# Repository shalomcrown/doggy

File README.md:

# doggy

Things to do with robot dogs. Firmware for a Freenove robot dog on **Raspberry Pi aarch64** (Pi 5 / 64-bit Raspberry Pi OS). The robot runtime is not a Windows target. Laptop LoRa operator clients are **x86_64** (Ubuntu DEB and Windows NSIS).

## Prerequisites

Run the installer once before building. First-class hosts: **Debian / Raspberry Pi OS Bookworm and Trixie**, and **Ubuntu 24.04**. Other distros are best-effort (unavailable packages are skipped; the script does not abort solely because the distro is untested).

```sh
./install-prereqs.sh                         # native on aarch64/arm64; cross otherwise
./install-prereqs.sh --mode native           # force Pi native packages
./install-prereqs.sh --mode cross            # Ubuntu aarch64 cross toolchain
./install-prereqs.sh --mode all              # native + cross
./install-prereqs.sh --mode windows        # nsis + nsis-common + go (Windows operator installer)
./install-prereqs.sh --mode simulator      # host compiler + Gazebo Harmonic (Ubuntu 22.04/24.04)
# Native and cross modes also install pipx and PlatformIO Core >= 6.2.0
# for ./build-watch.sh (Debian/Ubuntu apt PlatformIO is too old).
./install-prereqs.sh --dry-run               # preview without making changes
```

Native packages include compile deps (`cmake`, `ninja-build`, `g++`, `golang-go`) and dev tools (`qtcreator`, `git`, `vim`, `zssh`, `lrzsz`, `i2c-tools`). `golang-go` builds the `doggy-lora` sidecar (and `GOARCH=arm64` when packaging for the Pi). zlib, I2C SMBus, and IMU vectors are compiled from this tree — no `libdlib-dev`, `libi2c-dev`, or sysroot.

## Native Raspberry Pi build

```sh
cmake --preset native-debug
cmake --build --preset native-debug
./build/native-debug/doggy
```

Use `native-release` for an optimised binary.

## SSH to a dog as user `doggy`

The repo-root `./doggy` script is an SSH helper (not the firmware). It uses `zssh` when that is on `PATH`, otherwise `ssh`. The first argument is the target; further arguments are jump hosts. Host-key prompts are disabled (LAN convenience; connections are not authenticated against `known_hosts`).

```sh
./doggy doggy-1.local
./doggy doggy-1.local bastion.example
./doggy --dry-run doggy-1.local jump1 jump2
```

Login on the target is always `doggy@<host>`. Jump hops are passed as given (`user@hop` is allowed). A hop without `user@` uses OpenSSH’s default: the same user as the destination (`doggy`).

## Web UI

The firmware binary stays running and serves a single page (LAN, no login):

```sh
./build/native-debug/doggy
# https://<pi-ip>/   (port 443; http://<pi-ip>/ redirects)
# unprivileged local: DOGGY_HTTPS_PORT=8443 DOGGY_HTTP_PORT=8080 ./build/native-debug/doggy
```

- **Home** runs the homing pose (dog only)
- On a **dog**, the table lists each named servo (PWM and angle) with a slider and an **Off** button. The slider sends `POST /api/servos/{id}` `{ "angle" }` after **100ms idle**. Off sends `{ "enabled": false }` (PWM 0; angle unknown). The page refreshes PWM/angle from `GET /api/status` every 200 ms without resetting a slider you are dragging.
- On a **rover**, `/` is `rover.html`: a map sits to the left of the camera and a joystick to the right. The joystick sends `POST /api/drive` after 100 ms idle. Its inner circle is a dead zone (no steering, speed 0). Releasing the stick springs it to center. The map opens on Givat Shmuel, marks the latest GPS fix, and draws the current mission from stored 1 Hz telemetry. Previous missions (default 3) download as one zip. **New mission** starts a new file. The Pi keeps the files in `/var/lib/doggy/telemetry`; `telemetry.retain_hours` defaults to 168. Tile provider and key are stored in the browser (`localStorage`); OpenStreetMap needs no key, and a custom `http`/`https` template may use `{z}`, `{x}`, `{y}`, and `{key}`. Leaflet is served from the same machine as the page (the Pi, or the LoRa operator’s own disk) and is not transferred over LoRa. **Stop** and **Brake** sit to the right of the joystick. **Stop** (`POST /api/stop`) coasts motors and **Brake** (`POST /api/brake`) short-brakes them; both set commanded `speed`/`turn` to 0. After Stop the joystick returns to center. After Brake speed returns to zero and the stick keeps its turn. Either call, and per-motor Coast/Brake, zeros the per-motor speed sliders without sending a second `/api/drive`. Drive is an arcade mix: effective turn is `turn * (turn_gain_min + (1 - turn_gain_min) * |speed|)` (default `turn_gain_min` 0.25), then that value is added to the left motors and subtracted from the right, and both sides are scaled together if either would leave `[-1, 1]`. At rest a full steer is a reduced in-place spin; at full speed the same stick still uses full turn. Mixed magnitude maps linearly to 0–4095 PWM ticks; sign selects direction. The table shows each motor’s commanded PWM, enable, and configured wiring direction. The page also sends rover-only `POST /api/heartbeat` every 750 ms over Wi-Fi or LoRa. If the page closes or the link fails, the rover coasts after `robot.gcs_timeout_s` (default 3 seconds; 2–60). Direct API clients must heartbeat or reissue motion inside that timeout; `GET /api/status` never keeps motion alive.
- The camera panel plays WebRTC from MediaMTX (`GET /api/cameras`). MPEG-TS is recorded continuously while a stream is published (`GET /api/recordings`). **Snapshot** grabs a JPEG (`POST /api/snapshots`). Recordings close about every 15 minutes. Cleanup runs every 15 minutes: it drops files older than `media.retain_hours` (default 24) and deletes the oldest recordings until `media.min_free_mb` (default 512) stays free on that filesystem. An open segment is left alone. The page plays one stream, `cam0`. A USB camera that advertises a side-by-side MJPEG size (twice the width of another size at the same height) is preferred and published as MJPEG 1280×480, or 2560×720, or 1280×360, at 15 fps, software H.264, unrotated. If that feeder fails to start, or no such camera is present, the Raspberry Pi camera is used with the configured `cam0` size, rate, and rotation (`rpicam-vid`, hardware H.264, two buffers, denoise off). If that is also absent, one other USB camera is used: the lowest stable bus id, at 1280×720 and 15 fps, or the configured `cam0` size when both dimensions are smaller. The frame goes to `rtsp://127.0.0.1:8554/cam0`. Each selection is written to `doggy.log`: the Pi probe, every USB node (name, bus id, stereo or not, MJPEG sizes, chosen stereo size), the feeder that started, and a start that failed. Settings show one camera row: **Invert** (180°, on by default) and **Swap halves** (stereo only; exchanges the two eyes, then inverts if that is checked). Device, size, and frame rate stay automatic. `camera_pair` and the assign/swap routes remain for older config files and are not shown on the page. **Calibrate** (dog and rover) collects a chessboard from that same picture: both eyes when the feed is stereo, otherwise the one camera. The guide stays on the video; the controls sit beside it. **Save** writes `camera_calibration.yml` next to `doggy.json`. Nothing in the drive loop reads it yet. Calibration is not available over LoRa.
- The IMU section shows the last body MPU6050 sample (accel in g, gyro in °/s, temperature in °C).
- The battery section shows pack voltage from the ADS7830 (channel 0).
- The GPS section shows the latest fix from `GET /api/status` as a two-row table (headers, then values): status, UTC time, latitude, longitude, altitude above mean sea level, satellite count, fix quality, horizontal accuracy, and spoofing/jamming when the receiver reports them. It stays off until `gps.enabled` is true. Both configuration tables edit `enabled`, `type`, `device`, and `baud`; **Save** applies them without a service restart. `type` is `auto`, `nmea`, `ublox`, `septentrio`, or `novatel`. An empty `device` with `auto` uses one `/dev/serial/by-id` receiver whose name contains `u-blox` or `Septentrio` (several interfaces of that same receiver count as one; two different receivers are reported and not guessed). `nmea` and `novatel` need an explicit serial path. `baud` is the host rate (default 115200). The service only reads; it does not configure the receiver. Scan, selection, and open results are written to `doggy.log`.
- The title line (`<h1>` and the browser tab) shows `Doggy <version>` from `GET /api/status`; both pages show the current Linux time in UTC.
- **Configuration** loads `GET /api/config` and saves with `PUT /api/config`. Robot type is `DOG` or `ROVER` (missing type in the file is a dog); `robot.gcs_timeout_s` defaults to 3 and accepts 2–60 seconds. Changing type requires the system PIN, schedules a service restart, and the page tells you to **refresh** afterwards. Servo channels and each motor's PCA9685 `pwm`, `in2`, and `in1` channels apply immediately; motor channels must be unique and in 0–15. I2C bus and address changes are stored and take effect after a restart. Rover defaults use bonnet address `0x60` and clockwise motor triples FL 2/3/4, FR 5/6/7, RR 8/9/10, RL 11/12/13. **LoRa** (`lora.enabled`, `device`, `baud`, `band` `HF`|`LF`, `txch`, `rxch` 0–80, `lbt` 0–255) is stored the same way and does not restart `doggy`; the `doggy-lora` sidecar opens that USB serial port at the chosen baud (default 115200, 8N1) then applies `AT+LBT`, `AT+TXCH`, and `AT+RXCH`. LBT defaults to the module's factory value `0`. HF channel 18 is 868 MHz; LF channel 23 is 433 MHz. An 8–128 byte **air passphrase** (`lora.air_key`) is hashed with SHA-256 to derive the AES-256 key; GET JSON only reports `air_key_set`. Both ends must use the same strong passphrase. Set a **system PIN** here (4–64 characters, hashed in `doggy.json`).
- When a save is rejected, the status line shows the reason from the server (for example `Save failed: config lora.txch out of range`). Failed API calls are logged with their JSON error body; a config-write failure logs the file path server-side but does not return it.
- **Power** can restart `doggy.service`, reboot, or shut down the Pi. Each call is `POST /api/system` with the PIN (not the Unix password). Shutdown asks you to type `SHUTDOWN`. Privilege comes from a packaged polkit rule for user `doggy`.

HTTPS: `DOGGY_HTTPS_PORT` (default `443`). HTTP: `DOGGY_HTTP_PORT` (default `80`) only redirects to HTTPS. Unprivileged runs need ports above 1024. TLS files: `DOGGY_TLS_CERT` / `DOGGY_TLS_KEY`, or `tls.crt` / `tls.key` next to the JSON config (generated on first start if missing; browsers warn once on the self-signed cert). HTML: `DOGGY_WEB_ROOT` or `/usr/share/doggy` after the DEB is installed (`index.html`, `rover.html`, `lora.html`, `calibration.js`, `calibration.css`). Config: `DOGGY_CONFIG` or `/etc/doggy/doggy.json` (JSON; `robot.type`, `lora`, `gps` (`enabled`, `type`, `device`, `baud`), servo channels, motor `pwm`/`in2`/`in1` channels plus enable/direction, and I2C bus/address for the PCA9685, IMU, and ADS7830). If the file is missing, the process writes compiled defaults there (`postinst` creates `/etc/doggy` owned by `doggy`). A present but invalid file stops startup. `GET /api/config` returns that file shape (hex addresses) plus `system.pin_set` (never the PIN or hash). `PUT /api/config` overlays those fields; a type change also needs `pin` and returns 202 before restart. `POST /api/system/pin` sets the power PIN. `GET /api/status` includes `"type"`, the stamped `version`, hardware errors, cached IMU and battery readings, a `gps` fix, and either servo PWM/angle (`angle` is omitted when PWM is 0) or rover motors plus last `speed`/`turn`. Domain models are defined in `proto/doggy.proto` (HTTP uses ProtoJSON; the LoRa hop uses binary protobuf).

Existing rover configs using `motors.<name>.channel` must be migrated before
startup: replace `channel` with `pwm` and add `in2` and `in1` for every motor.
Also set `i2c.servo_board.address` to `0x60` for the Adafruit bonnet if an older
config persisted the previous `0x40` default.

The DEB also installs `doggy-lora` (`User=doggy`, `dialout`). Robot mode reads public radio fields from `https://127.0.0.1/api/config` (self-signed cert) and the air passphrase from `/etc/doggy/doggy.json` (the passphrase is not in public GET JSON). It opens `lora.device` at `lora.baud` (115200 8N1 unless you change it), writes Waveshare AT (`+++`, 200 ms pause, then `AT+LBT=0..255`, `AT+TXCH`, `AT+RXCH`, `AT+EXIT`, waiting for `OK` after each command), **keeps the port open**, and answers operator HTTP requests over LoRa (binary protobuf + AES-256-GCM).

Laptop operator (separate packages, not the Pi DEB): `./build-operator.sh` builds an **amd64** Ubuntu package `shaloms-doggy-lora-operator` and/or a Windows NSIS installer. Both bind `http://127.0.0.1:8765/`. Ubuntu enables `doggy-lora-operator.service` and a desktop icon. Windows installs a LocalSystem service `DoggyLoraOperator` (needed for USB serial) and Start Menu/Desktop shortcuts to that URL. Settings live in `/var/lib/doggy-lora/lora.json` or `%ProgramData%\doggy\lora.json`. `/api/lora` is that local file; dog/rover `/api/*` is proxied over the radio. Set the same air passphrase on both ends.

## Protobuf models and transports

`proto/doggy.proto` is the single source of truth for configuration, status, commands, API payloads, and the LoRa request/response envelope. Do not hand-write parallel C++ or Go wire-model classes.

- CMake runs `protoc` and generates C++ into `build/<preset>/generated/doggy.pb.{h,cc}`.
- `protoc-gen-go` generates `lora/internal/pb/doggy.pb.go`; generated protobuf files are build output and are not edited by hand.
- The HTTPS API serializes those generated messages as ProtoJSON, preserving the `.proto` field names.
- The LoRa air hop serializes generated `AirRequest` and `AirResponse` messages as binary protobuf. It then applies AES-256-GCM, fragments the ciphertext into COBS-delimited frames, and protects each frame with CRC32C.
- Each fragment requires an ACK and is sent at most three times. Missing ACKs use bounded exponential waits (1.5, 3, then 6 seconds) plus up to 500 ms of jitter to avoid synchronized retransmissions.
- Native builds can build `protoc` from the pinned protobuf source fetched by CMake. Cross-builds use the host `protoc` because an aarch64 target executable cannot run on the amd64 build host.

Logs go to `/var/log/doggy/doggy.log` (override with `DOGGY_LOG_DIR`). The file is rolled on every start and when it exceeds the size cap; 10 files are kept and rolled copies are named `doggy-YYYY-MM-DD-HHMM.log.gz`. The log directory is `0755` and log files are world-readable (`0644`). Every `/api/...` request is logged with the **remote IP** first (`127.0.0.1` is `doggy-lora` polling `GET /api/config` every 5 s in robot mode, not the web UI). Endpoints with a request body log one-line JSON (PIN and air key redacted on config/system calls); `GET /api/config` logs one-line public JSON from the response. HTTP failures (4xx/5xx) and hardware errors are logged at error severity. The packaged unit sets `LogsDirectory=doggy` so the directory is owned by user `doggy`.

## Package and install on a remote Pi

```sh
./build.sh                                  # native-release on aarch64; cross otherwise
./install.sh user@hostname                  # newest shaloms-doggy_*.deb under build/
./install.sh user@hostname path/to.deb      # explicit package
./install.sh --dry-run user@hostname        # print scp/ssh only
```

`./build.sh` uses `uname -m`: `aarch64` / `arm64` → `native-release`; any other arch → `ubuntu-aarch64-cross`. No sysroot. The `.deb` is Debian architecture `arm64` even when packaged on an amd64 host. `--dry-run` prints the cmake commands without running them. Equivalent manual commands:

```sh
cmake --preset native-release
cmake --build --preset native-release --target package
```

## Watch firmware

`watch/` is a separate PlatformIO project for the LilyGO T-Watch S3 and
Waveshare ESP32-C6 Touch AMOLED 2.06. It is not packaged in the Pi DEB.

```sh
./build-watch.sh all
./install-watch-s3.sh                 # flash LilyGO T-Watch S3
./install-watch-c6.sh                 # flash Waveshare ESP32-C6
```

The first slice provides an LVGL clock, ESP-Touch v2 Wi-Fi provisioning, NTP,
and a swipe-accessible fixed UTC-offset settings page (default UTC+3:00). A
second swipe opens **Doggys**, where the watch browses Avahi `_doggy._tcp`
advertisements and stores the selected robot identity. It does not yet send
HTTPS control. See `watch/README.md` for flashing and hardware verification.
Flash is pinned to esptool 5.3.1 (5.4.0 crashes mid-upload). Rover control and
watch LoRa are deferred.

The script copies the `.deb` to `/tmp` over SSH and runs `sudo apt-get install`. Copy and install share one SSH connection (ControlMaster), so the login password is asked once; `sudo` may still ask once if the account is not passwordless. The package creates system user `doggy` if needed, enables I2C in `/boot/firmware/config.txt` when missing, and may ask you to reboot. It then enables and **restarts** `doggy.service` and `doggy-lora.service` (`User=doggy`, I2C via the `i2c` group, USB serial via `dialout`) before any reboot prompt. An upgrade does not stop the unit in `prerm`, so a failed `postinst` cannot leave the dog down.

CMake configure fetches cpp-httplib v0.52.0, plog 1.1.11, zlib 1.3.1, nlohmann/json 3.11.3, and Mbed TLS 3.6.7 (needs network once, or set `FETCHCONTENT_SOURCE_DIR_CPP_HTTPLIB` / `FETCHCONTENT_SOURCE_DIR_PLOG` / `FETCHCONTENT_SOURCE_DIR_ZLIB` / `FETCHCONTENT_SOURCE_DIR_JSON` / `FETCHCONTENT_SOURCE_DIR_MBEDTLS`). The system PIN is hashed with Mbed TLS SHA-256; HTTPS uses the same Mbed TLS tree.

Each build stamps the version as `1.0.0-YYYY-MM-DD-HHMM-<short-git-hash>` (local time). The DEB filename uses the same string. The process prints it when it starts; `GET /api/status` and the web title line show it too.

## Target on-disk layout

After `apt-get install` of `shaloms-doggy` the Pi has:

```
/usr/bin/doggy                         firmware (systemd ExecStart)
/usr/bin/doggy-lora                    LoRa sidecar (robot mode on the Pi)
/usr/share/doggy/index.html            dog web UI
/usr/share/doggy/rover.html            rover web UI
/usr/share/doggy/lora.html             LoRa setup UI
/etc/systemd/system/doggy.service      unit (User=doggy)
/etc/systemd/system/doggy-lora.service sidecar unit (User=doggy, dialout)
/etc/avahi/services/doggy.service      DNS-SD `_doggy._tcp` on HTTPS 443
/etc/doggy/                            created at install (User=doggy, mode 0755)
/etc/doggy/doggy.json                  firmware + robot-side LoRa configuration
/etc/doggy/tls.crt                     self-signed cert (created on first start)
/etc/doggy/tls.key                     TLS private key (mode 0600, not in the DEB)
/var/log/doggy/                        created at install and on start
/var/log/doggy/doggy.log               current log
/var/log/doggy/doggy-YYYY-MM-DD-HHMM.log.gz
/etc/modules-load.d/shaloms-doggy-i2c.conf   only if postinst enabled I2C
```

The package does not install the repo-root `./doggy` SSH helper. `postinst` may edit `/boot/firmware/config.txt` (or `/boot/config.txt`) to turn on I2C; that file is not owned by the package.

`cmake --install` without packaging uses prefix `/usr/local` (`/usr/local/bin/doggy`, `/usr/local/share/doggy/index.html`) unless you set `CMAKE_INSTALL_PREFIX`.

## Ubuntu → Raspberry Pi aarch64 cross-build

On a non-Pi host, `./install-prereqs.sh` installs `g++-aarch64-linux-gnu`. Then:

```sh
./build.sh
```

or:

```sh
cmake --preset ubuntu-aarch64-cross
cmake --build --preset ubuntu-aarch64-cross --target package
```

No Pi sysroot: zlib is fetched by CMake, I2C uses the kernel `I2C_SMBUS` ioctl, and IMU math uses `Vec3` instead of dlib.

## Laptop LoRa operator (Ubuntu + Windows)

x86_64 only. Does not build Pi firmware. Needs `golang-go`; Windows NSIS also needs `nsis` and `nsis-common` (stubs and plugins such as MUI2 and nsExec — `./install-prereqs.sh --mode windows`).

```sh
./build-operator.sh                # Ubuntu DEB and Windows NSIS
./build-operator.sh linux         # shaloms-doggy-lora-operator_*.amd64.deb
./build-operator.sh windows        # doggy-lora-operator-*-win64.exe
./build-operator.sh --dry-run
```

CMake presets: `operator-linux-amd64`, `operator-windows-amd64` (`--target package`). The Windows binary is `GOOS=windows GOARCH=amd64` with `CGO_ENABLED=0` (no MinGW). The installer creates the `DoggyLoraOperator` service (LocalSystem, localhost HTTP) using CPack NSIS, same idea as other CPack NSIS projects.

## Host simulator

`./build-simulator.sh` builds `doggy-sim` for the machine you are on. It does not package the Pi. The simulator build uses the system protobuf so Gazebo and doggy-sim can share one process.

```sh
./install-prereqs.sh --mode simulator
./build-simulator.sh
./build/simulator/doggy-sim
```

The page is plain HTTP on `127.0.0.1:8080` (no TLS, no root). The Pi binary is unchanged and still uses HTTPS. Settings live in `~/.config/doggy/simulator.json` and are separate from `doggy.json`. Defaults: full stick `2.0` m/s, track `0.20` m, origin Givat Shmuel. `DOGGY_SIM_SPAWN=0` serves the page without starting Gazebo.

`doggy-sim` starts Gazebo and subscribes to odometry, IMU, and the two cameras over gz-transport. It publishes `gz.msgs.Twist` on `/model/doggy_rover/cmd_vel`. A command older than about half a second becomes a zero twist. The world is `sim/worlds/street.sdf` (road, shoulder, curb, pavement, one obstacle). The map shows a GPS fix with a 1 Hz error of at most 0.2 m and a 0.01 Hz error of at most 2.5 m. Simulator telemetry is stored in `~/.config/doggy/simulator/telemetry` unless `DOGGY_TELEMETRY_DIR` is set. Truth pose stays inside the simulator for a later filter. Per-motor sliders do not move the simulated rover; arcade drive does.

The two Gazebo cameras are fed through FFmpeg into a loopback MediaMTX (`usb_left` and `usb_right`). `/api/cameras` then returns `http://127.0.0.1:18889/<id>/whep`, which the rover page already plays. That MediaMTX does not use TLS and does not record. The Pi camera URLs stay `https`. `./install-prereqs.sh --mode simulator` installs MediaMTX v1.21.0 under `~/.local/lib/doggy/mediamtx`.

## Tests

CTest covers installer scripts, the SSH helper, PWM math, HTTP API, and log rotation (no I2C):

```sh
cmake --preset native-debug
ctest --preset native-debug
```

Or: `bash tests/install-prereqs.test.sh`

## Source layout

```
proto/doggy.proto             protobuf source of truth for all wire models
src/                          C++ firmware, hardware drivers, HTTPS API, config
lora/cmd/doggy-lora/          Go sidecar/operator executable and mode startup
lora/internal/air/            encrypted protobuf air session, frames, COBS, CRC
lora/internal/atcmd/          Waveshare command generation and reply handling
lora/internal/hop/            robot/operator air-hop runtime
lora/internal/operator/       localhost operator HTTP server and API proxy
lora/internal/pb/             generated Go protobuf package
lora/internal/radio/          serial radio ownership and apply loop
lora/internal/serialport/     Linux/Windows serial configuration
lora/internal/settings/       shared LoRa JSON settings
web/                          dog, rover, and LoRa setup pages
packaging/                    systemd, desktop, polkit, Debian, and NSIS assets
cmake/                        protobuf generation, packaging, and toolchains
tests/                        C++ and shell integration/regression tests
CMakeLists.txt                firmware, sidecar, generated models, tests, install
CMakePresets.json             native, cross, Linux operator, Windows operator
sim/                          Gazebo street world and gz-transport bridge
build.sh / build-operator.sh / build-simulator.sh
                              firmware, laptop, and host simulator entry points
install.sh                    newest firmware-DEB remote installer
install-watch-s3.sh / -c6.sh  USB flash for each watch board
```

CMake stays at the repository root. Generated files belong under `build/` or
`lora/internal/pb/`; edit `proto/doggy.proto`, not generated `doggy.pb.*` files.
Installed paths are listed under **Target on-disk layout**.

## LoRa setup

The robot and operator each need a Waveshare USB-TO-LoRa-xF device. Configure
the Pi at `https://<pi-ip>/` and the laptop at
`http://127.0.0.1:8765/`:

1. Select **Enabled** and enter the local serial device
   (`/dev/ttyACM0`, `/dev/ttyUSB0`, or `COM3`) and host baud (normally
   `115200`, 8N1).
2. Select the module family: **HF** (850–930 MHz) or **LF** (410–490 MHz).
3. Set TXCH and RXCH on both ends so the radios agree. HF frequency in MHz is
   `850 + channel`; LF frequency is `410 + channel`.
4. Set **LBT** to the module's unsigned 8-bit value (0–255). Start with `0`,
   the factory default. The module accepts the full range but does not document
   its units; do not assume that `1` means simply “enabled”. Apply another value
   only when you have vendor or local regulatory guidance for that radio.
5. Enter the same strong 8–128 byte air passphrase on both ends. It is
   write-only in HTTP responses and is hashed with SHA-256 to derive the
   32-byte AES-256-GCM key.
6. Save both ends. The helper enters command mode with `+++`, waits 200 ms,
   sends `AT+LBT`, `AT+TXCH`, `AT+RXCH`, and `AT+EXIT` sequentially, and waits
   for `OK` before each next command.

Migration: configurations created with the experimental boolean setting must
replace `"listen_before_talk": true|false` with `"lbt": 0`. Legacy fields are
rejected so a stale configuration cannot silently apply the problematic value 1.
Edit `/etc/doggy/doggy.json` on the Pi and `/var/lib/doggy-lora/lora.json` on a
Linux operator host. Startup names the file and the rejected field, for example
`/etc/doggy/doggy.json: invalid config JSON: INVALID_ARGUMENT:(lora)
listen_before_talk: Cannot find field.`

On the Pi, verify `doggy.service` and `doggy-lora.service`; on Linux operator
packages verify `doggy-lora-operator.service`. Service logs show AT commands
and replies but never the air passphrase. If diagnosing a module manually,
enter command mode and use `AT+HELP`, `AT+LBT?`, `AT+TXCH?`, and `AT+RXCH?`,
then finish with `AT+EXIT`.

The HF module can power up with generalized 915 MHz settings. For the Israeli
installation described here, constrain operation to 917–920 MHz (HF channels
67–70). Confirm current LBT and other regulatory requirements for the deployment
location; this README is not a substitute for radio certification.

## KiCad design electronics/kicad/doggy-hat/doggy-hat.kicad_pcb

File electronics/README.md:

# Electronics of doggy / rover

## Design of Pi hat for doggy/rover

A Raspberry Pi HAT for **Pi 3 Model B+** and later 40-pin boards (Pi 3B+, Pi 4, Pi 5). It uses the HAT mounting holes, a stacking 40-pin header, and an ID EEPROM. The board may extend past the 65 mm × 56.5 mm HAT outline. Sixteen servo connectors do not fit inside that outline, so the extension is expected. Keep the Pi 3 CSI ribbon, USB, Ethernet, HDMI, and the SD card usable.

The device bus is I2C1 on GPIO2/GPIO3. GPIO0/GPIO1 stay the HAT ID bus.

### Two boards

The circuit is two boards on one stacking GPIO header. The lower board is a standard HAT: pack input, Pi 5 V, hat 3.3 V, the ID EEPROM, the IMU, and the barometer. The upper board is that HAT plus 20 mm on the left (away from USB and Ethernet) and a 10 mm strip on the far edge from about x = 118 mm to the HDMI end. That strip holds the motor screws. The sixteen servo headers stay on a 5.08 mm pitch along the far edge. The left ear holds the wheel connectors, the compass connector, and the USB-C receptacle for the RP2040. The battery screw is on the lower board, at the far-left corner, with the wire leaving into the gap where the upper board is not extended.

Actuator current does not use the GPIO header. A second connector, J30, sits at the same place on both boards, inboard of the GPIO header. Its paralleled pins carry the pack. A generic 1 A pin is not enough: the header has to be rated so those pins together carry 15 A, and the stacking pins have to be long enough for two boards.

| J30 pins | Net | Role |
|---|---|---|
| 1–8 | `VBAT_LOAD` | Pack after the shunt, fuse, and ideal diode |
| 9–16, 20 | `GND` | Common return |
| 17–18 | `+3V3` | Hat 3.3 V, made on the lower board |
| 19 | `ACT_DISABLE` on the lower board, `ACT_LATCH` on the upper | Latch output. The e-stop sits between those two names |
| 21–22 | `I2C1_SDA`, `I2C1_SCL` | Device side of the 47 Ω resistors |
| 23–24 | `+5V_PI` | Buck output, before the ideal diode, for the RP2040 mux |

The upper header records pins 2 and 4 as `+5V_HDR`. That is the Pi side of the ideal diode. It is not joined to `+5V_PI`. I2C reaches the upper board only through J30, after the series resistors. The upper header does not connect pins 3, 5, 27, or 28. Only the lower board connects `ID_SD` and `ID_SC`.

The e-stop is on the upper board. It is a normally closed switch in the actuator-disable line, with a 100 kΩ pull-up to hat 3.3 V, so an open switch forces the rails off. The Pi rail stays up. The footprint on the sheet is a small tactile switch, not a panel e-stop. If the upper board has no 3.3 V, that pull-up does nothing and the rail's own enable divider can still turn the buck on; driving the disable transistor is what holds the rail off.

The 10 mm screw strip sits one stacking height above the HDMI end of a Pi 3. Check a full-size HDMI plug before ordering the boards. The lower board does not grow.

Projects: `electronics/kicad/doggy-lower/` and `electronics/kicad/doggy-upper/`. The sheets stay in `electronics/kicad/doggy-hat/`. `build_split.py` rewrites the generated link sheets, the sensor split, and the e-stop edit on `pack.kicad_sch`. Do not rerun `generate_schematic.py`.

### Requirements

* One battery input: a screw-terminal pair. The Pi is powered only through the header.
* Pack voltage and total input current, one INA228. Cutoff is a software setting (cell count or minimum voltage). The pack is 4S today and may be up to 8S.
* 16 servo channels for SG92R-class servos, on a regulated 5 V rail.
* 4 DC motor channels, 1 A stall each, motor voltage set in the 5–12 V range.
* IMU, compass, and barometer.
* One sensor per wheel, wired for either a single channel or a quadrature pair. The mode is a firmware setting.
* I2C1 uses the pull-ups already fitted on the Pi. The ID bus has its own pull-ups.

### Power

* **Input:** one screw-terminal pair, battery positive and negative. That is the only external pack connector. The boards join through J30. The Pi's own USB power socket stays unused while the hat is fitted.
* **Range:** the input path is rated for a 4S pack at cutoff through an 8S pack at full charge. Electrical window is 10 V to 36 V operating, 40 V absolute, so 8 × 4.2 V (33.6 V) still has margin. Software may set the cutoff higher. It cannot rely on the regulators below 10 V.
* **INA228** high-side shunt on this input, ahead of every regulator. Terminals, shunt, and input copper are sized for 15 A, which covers the Pi, sixteen servos at stall, and four motors at stall while the pack is at the low end of the window.
* Reverse-polarity protection on the pack input. A fuse on the pack input.
* **Pi rail:** buck to 5 V at 5 A, into header pins 2 and 4, with ground on the header ground pins. An ideal diode on this feed so the hat and a USB supply on the Pi cannot back-feed each other. The hat's fuse is the protection: back-powering bypasses the Pi 3 polyfuse. The hat does not draw logic power from the Pi 3.3 V pin.
* **Hat 3.3 V:** its own regulator from the Pi 5 V rail, for the PCA9685s, IMU, barometer, INA228, encoder microcontroller, and the ID-bus pull-ups.
* **Servo rail:** buck to 5.0 V. SG92R-class servos run from 4.8 V to 6.0 V. Tower Pro quotes torque at 4.8 V and does not state stall current; allow 0.75 A stall per servo. The rail, its fuse, the connectors, and the copper are sized for 16 × 0.75 A (12 A).
* **Motor rail:** a regulator set by resistors to a fixed voltage in the 5–12 V range, at 4 A continuous (4 × 1 A stall). It has to hold that voltage across the whole pack window, including a 12 V rail while a 4S pack is near cutoff, so this regulator is a buck-boost. The chosen voltage is an assembly setting, recorded on the board.
* Servo and motor current return to their own rails. Header ground is the logic reference. The three rails join the pack at one point.
* Bulk capacitance at the motor drivers.
* **E-stop:** a switch, independent of the Pi, drops the servo rail and the motor rail. The Pi rail stays up.
* **Pack cutoff:** firmware writes the INA228 alert from the software setting, then arms a latch. The latch drops the Pi rail and both actuator rails, and it stays off until a manual reset. The alert covers low pack voltage and overcurrent. Actuator rails stay off until the firmware has armed the latch and the pack is above the cutoff.

### Software settings

These are firmware configuration, not resistors:

* Pack cutoff, defaulting to the present 4S pack. Either a cell count from 4 to 8, turned into a voltage with a per-cell floor, or an explicit minimum pack voltage. The INA228 alert uses that voltage.
* Wheel sensors: quadrature, or single channel. Single channel counts pulses on A and takes direction from the motor command.

### Servos and motors

The PCA9685 produces 3.3 V PWM. It does not switch motor current. One PCA9685 has 16 channels, and the servos use all of them, so the motors need a second PCA9685. The Pi has two hardware PWM channels, which is not enough for four motors.

* **Servo PCA9685** at `0x40`. Sixteen 3-pin headers (signal, 5 V servo power, ground), grouped to match the leg harness. Series resistor on each signal. `OE` is pulled up, so the outputs stay off until the RP2040 drives it.
* **Motor PCA9685** at `0x60`. Four H-bridge channels, each rated for at least 1 A continuous. Each motor uses three logic signals: `PWM`, `IN1`, `IN2`. Its `OE` is pulled up on its own net, separate from the servo `OE`.
  * `IN1`/`IN2` opposite: forward or reverse, speed from `PWM`
  * both high: short brake
  * both low: coast
* The RP2040 drives servo `OE`, motor `OE`, and TB6612 `STBY`. `STBY` is pulled down, and the TB6612 treats that pin low as standby, so the wheels coast until firmware drives it. Firmware returns all three to the off state if the Pi stops refreshing within about 100 ms.

This split matches the firmware: the dog uses a PCA9685 at `0x40` for servos, and the rover uses `0x60` with `pwm` / `in1` / `in2` per motor.

### INA228

Address `0x45` (`A1` and `A0` tied to VS), clear of both PCA9685 addresses. The alert pin drives the cutoff latch. The Pi also reads pack voltage and current over I2C.

### Sensors

* **IMU** at `0x68` on the hat (the body MPU6050 the firmware already reads). Data-ready pin to a Pi GPIO.
* **Barometer** at `0x76` on the hat.
* **Compass** on a small board at the end of an I2C cable, away from motor current and the pack. On this PCB it would read the motors. Address `0x0D` (QMC5883L) or `0x1E` (HMC5883L). No pull-ups on that board. Cable length under 30 cm.
* **Wheels:** one connector per wheel, with A, B, 3.3 V, and ground. A single-channel sensor uses A and leaves B open. A quadrature sensor uses A and B in the same package. Four LM393 channels cover the single-channel case; quadrature uses eight comparator channels into the microcontroller. Open-collector outputs are pulled up to hat 3.3 V, then a 3.3 V Schmitt trigger into the microcontroller. The microcontroller publishes counts and a reset over I2C. The Pi reads counts over I2C. Interrupt to a Pi GPIO.

### I2C

GPIO2 and GPIO3 already have about 1.8 kΩ pull-ups to 3.3 V on the Pi. A second pair on the hat would push the sink current past the 3 mA I2C limit, so I2C1 has no pull-ups on this board.

* Run the device bus at 400 kHz. With the Pi's pull-ups and the devices on this hat, rise time stays inside Fast-mode for a compass cable under 30 cm.
* Series resistors of 47 Ω in SDA and SCL next to the GPIO header, to damp the edges.
* The compass board adds capacitance and no pull-ups.

The ID bus is separate. ID_SD and ID_SC connect only to a 3.3 V, 16-bit-address, non-paged EEPROM at `0x50`, plus 3.9 kΩ pull-ups to hat 3.3 V. The schematic uses a 24LC32A (CAT24C32 equivalent) with A0, A1, and A2 tied to ground. Write-protect goes to a test point, pulled up. The EEPROM is specified for 100 kHz and does not clock-stretch. Nothing else connects to those pins.

### I2C map

| Device | Bus | Address |
|---|---|---|
| HAT EEPROM (24LC32A) | ID (GPIO0/GPIO1) | `0x50` |
| PCA9685, servos | I2C1 | `0x40` |
| PCA9685, motors | I2C1 | `0x60` |
| INA228 | I2C1 | `0x45` |
| IMU | I2C1 | `0x68` |
| Barometer | I2C1 | `0x76` |
| Compass (off-board) | I2C1 | `0x0D` or `0x1E` |
| RP2040 encoder microcontroller | I2C1 | `0x33` |

### Header pins left for later

* UART on GPIO14/GPIO15 and a PPS input, so GPS can leave USB later. The receiver stays off this board. On Pi 3 this UART is shared with Bluetooth, so Bluetooth has to move if both are on.
* LoRa stays on USB. No radio on the hat.

### Bring-up

* LEDs and test points for pack input, Pi 5 V, hat 3.3 V, servo 5 V, and the motor rail.
* Test points on servo `OE`, motor enable, the cutoff latch, and EEPROM write-protect.

### Datasheets

Before a chip is placed in the schematic, its manufacturer datasheet is in `datasheets/` at the repo root. Use a file already there when it matches the part. Otherwise download it as part of implementation. Symbols, footprints, and pin wiring come from that datasheet.

The sheets live in `electronics/kicad/doggy-hat/`. The lower project is `electronics/kicad/doggy-lower/` and the upper project is `electronics/kicad/doggy-upper/`. `servos.kicad_sch` draws the sixteen 3-pin servo headers, grouped by leg. `motors.kicad_sch` draws the four motor screw terminals. Datasheets for the parts on those sheets:

`INA228.pdf`, `TPS54560B.pdf`, `LM5176.pdf`, `LM74700-Q1.pdf`, `CSD18540Q5B.pdf`, `LR8.pdf`, `AMS1117.pdf`, `2N3904.pdf`, `SN74HC00.pdf`, `SN74HC14.pdf`, `LM393.pdf`, `PCA9685.pdf`, `TB6612FNG_datasheet_en_20121101.pdf`, `MPU-6050.pdf`, `BMP280.pdf`, `24LC32A.pdf`, `RP2040.pdf`, `RP2040-hardware-design.pdf`, `W25Q32JV.pdf`.

Also in `datasheets/`, not placed on this hat: `DS_SX1261-2_V1.2.pdf`, `raspberry_pi_schem1.png`.

### Encoder microcontroller

**RP2040.** The encoders are low resolution, and the board has to be programmed with a normal USB cable. The RP2040 bootloader is in mask ROM: hold BOOTSEL, plug in USB, and copy a UF2 file. A blank flash chip is enough. No UPDI, SWD, or ISP adapter.

* QFN-56 on this board, with a USB-C device receptacle on the board edge, a BOOTSEL button, a 12 MHz crystal, and a QSPI flash (2 MB is enough). USB data goes only to the RP2040. It is not wired to the Pi.
* Follow the Pico reference for the flash, crystal, and BOOTSEL wiring. Those parts come from the RP2040 and flash datasheets at implementation.
* I2C slave at `0x33`. One interrupt output to the Pi. Quadrature or single-channel is the firmware setting. PIO counts the edges.
* The slave must not clock-stretch. Pi 3 I2C loses the bus when a slave holds the clock. Counts stay in memory and the transfer only shifts those bytes out.
* Power: the hat 3.3 V rail runs the chip when the pack is on. USB VBUS can power the RP2040 alone, through its own regulator, so the chip can be programmed with no battery connected. The rest of the hat stays off in that case.
* An ESP32 is not used. Its radio would sit next to the compass and the motor PWM.

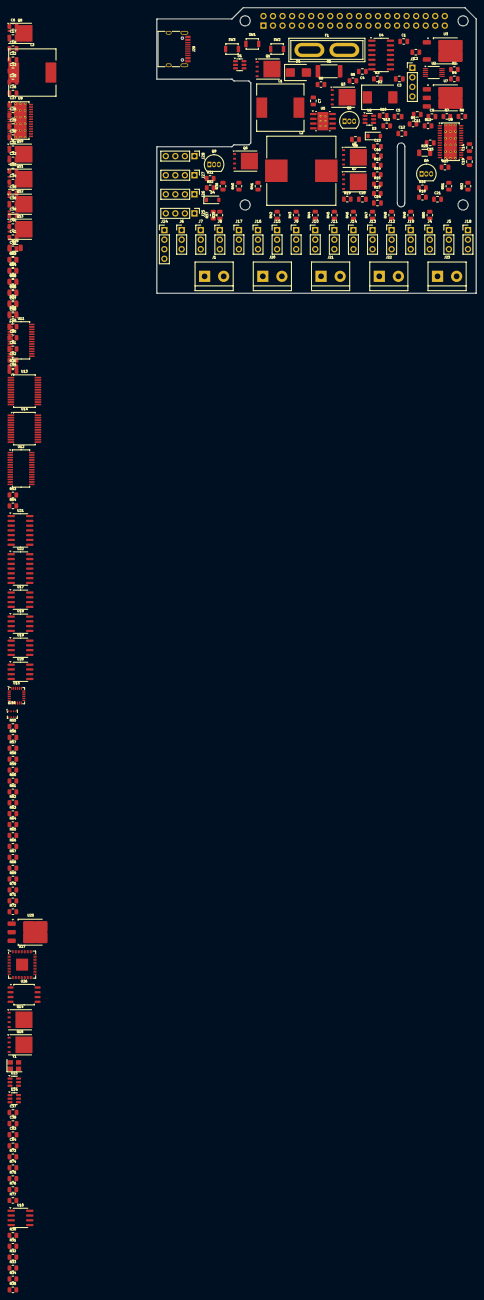
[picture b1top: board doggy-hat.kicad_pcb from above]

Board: 2 copper layers, 85.0 x 76.0 mm, 219 parts (1 on the bottom side), 185 nets, no tracks yet.

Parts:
C1, C2, C3, C4, C5, C9, C12, C13, C15, C20, C21, C23, C28, C29, C30, C33, C35, C36, C37, C38, C41, C42, C43, C44, C45, C46, C47, C48, C49, C50, C51, C55: 100nF; C_0805_2012Metric
C6: 4.7nF; C_0805_2012Metric
C7, C10, C11, C39, C40: 10uF; C_0805_2012Metric
C8, C18, C19, C26, C27: 22uF; C_0805_2012Metric
C14, C22, C52: 1uF; C_0805_2012Metric
C16, C24: 220pF; C_0805_2012Metric
C17, C25, C34: 10nF; C_0805_2012Metric
C31, C32: 100uF; C_0805_2012Metric
C53, C54: 15pF; C_0805_2012Metric
D1: SMBJ36A; D_SMB
D2: PDS760; D_SMC
D3, D4: 5.1V; D_SOD-123
F1: 20A; Fuse_Blade_ATO_directSolder
J1: BAT; TerminalBlock_bornier-2_P5.08mm
J2: PI_GPIO; PinSocket_2x20_P2.54mm_Vertical
J3: GPS_LATER; PinHeader_1x04_P2.54mm_Vertical
J4: spare 0; PinHeader_1x03_P2.54mm_Vertical
J5: spare 1; PinHeader_1x03_P2.54mm_Vertical
J6: FL knee; PinHeader_1x03_P2.54mm_Vertical
J7: FL hip; PinHeader_1x03_P2.54mm_Vertical
J8: FL waist; PinHeader_1x03_P2.54mm_Vertical
J9: RL knee; PinHeader_1x03_P2.54mm_Vertical
J10: RL hip; PinHeader_1x03_P2.54mm_Vertical
J11: RL waist; PinHeader_1x03_P2.54mm_Vertical
J12: RR waist; PinHeader_1x03_P2.54mm_Vertical
J13: RR hip; PinHeader_1x03_P2.54mm_Vertical
J14: RR knee; PinHeader_1x03_P2.54mm_Vertical
J15: FR waist; PinHeader_1x03_P2.54mm_Vertical
J16: FR hip; PinHeader_1x03_P2.54mm_Vertical
J17: FR knee; PinHeader_1x03_P2.54mm_Vertical
J18: spare 14; PinHeader_1x03_P2.54mm_Vertical
J19: head neck; PinHeader_1x03_P2.54mm_Vertical
J20: FL screw; TerminalBlock_bornier-2_P5.08mm
J21: FR screw; TerminalBlock_bornier-2_P5.08mm
J22: RR screw; TerminalBlock_bornier-2_P5.08mm
J23: RL screw; TerminalBlock_bornier-2_P5.08mm
J24: COMPASS; PinHeader_1x04_P2.54mm_Vertical
J25: FL; PinHeader_1x04_P2.54mm_Vertical
J26: FR; PinHeader_1x04_P2.54mm_Vertical
J27: RR; PinHeader_1x04_P2.54mm_Vertical
J28: RL; PinHeader_1x04_P2.54mm_Vertical
J29: RP2040_USB; USB_C_Receptacle_HRO_TYPE-C-31-M-12
L1: 10uH; L_12x12mm_H6mm
L2: 4.7uH; L_Wuerth_HCI-1890
L3: 4.7uH; L_12x12mm_H8mm
MH1, MH2, MH3, MH4: MountingHole_2.7mm_M2.5
Q1, Q3, Q5, Q6, Q7, Q8, Q10, Q11, Q12, Q13, Q14, Q15: CSD18540Q5B; TDSON-8-1
Q2, Q4, Q9: 2N3904; TO-92_Inline
R1: 10mohm 3W; R_2512_6332Metric
R2, R5, R10, R11, R14, R19, R23, R28, R36, R53, R55, R56, R57, R59, R61, R63, R65, R67, R69, R71, R73: 10k; R_0805_2012Metric
R3: 16.2k; R_0805_2012Metric
R4, R25: 10.0k; R_0805_2012Metric
R6, R17, R26, R32, R54, R58, R60, R62, R64, R66, R68, R70, R72: 100k; R_0805_2012Metric
R7: 243k; R_0805_2012Metric
R8, R15: 105k; R_0805_2012Metric
R9, R16: 20.0k; R_0805_2012Metric
R12, R21: 27.0k; R_0805_2012Metric
R13, R22: 200k; R_0805_2012Metric
R18, R27: 14.0k; R_0805_2012Metric
R20: 5mohm; R_1206_3216Metric
R24: 140k; R_0805_2012Metric
R29: 12mohm; R_1206_3216Metric
R30, R31: 47; R_0805_2012Metric
R33, R34: 3.9k; R_0805_2012Metric
R35: 1k; R_0805_2012Metric
R37, R38, R39, R40, R41, R42, R43, R44, R45, R46, R47, R48, R49, R50, R51, R52: 220; R_0805_2012Metric
R74, R75: 27; R_0805_2012Metric
R76, R77: 5.1k; R_0805_2012Metric
SW1: RESET; SW_SPST_B3U-1000P
SW2: ESTOP_NC; SW_SPST_B3U-1000P
SW3: BOOTSEL; SW_SPST_B3U-1000P
U1, U6, U23, U24: LM74700-Q1; SOT-23-6
U2: INA228; VSSOP-10_3x3mm_P0.5mm
U3: LR8K4-G; TO-252-2
U4: 74HC00; SOIC-14_3.9x8.7mm_P1.27mm
U5: TPS54560B; Texas_R-PDSO-G8_EP2.95x4.9mm_Mask2.4x3.1mm_ThermalVias
U7, U25: AMS1117-3.3; TO-252-3_TabPin2
U8, U9: LM5176; HTSSOP-28-1EP_4.4x9.7mm_P0.65mm_EP3.4x9.5mm_ThermalVias
U10: 24LC32A; SOIC-8_3.9x4.9mm_P1.27mm
U11, U12: PCA9685PW; TSSOP-28_4.4x9.7mm_P0.65mm
U13, U14: TB6612FNG; SSOP-24_5.3x8.2mm_P0.65mm
U15: MPU-6050; InvenSense_QFN-24_4x4mm_P0.5mm
U16: BMP280; Bosch_LGA-8_2x2.5mm_P0.65mm_ClockwisePinNumbering
U17, U18, U19, U20: LM393; SOIC-8_3.9x4.9mm_P1.27mm
U21, U22: 74HC14; SOIC-14_3.9x8.7mm_P1.27mm
U26: W25Q32JVSS; SOIC-8_5.23x5.23mm_P1.27mm
U27: RP2040; QFN-56-1EP_7x7mm_P0.4mm_EP3.2x3.2mm
Y1: ABM8-272-T3; Crystal_SMD_3225-4Pin_3.2x2.5mm

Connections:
+3V3: C11.1, C28.1, C29.1, C30.1, C35.1, C36.1, J24.1, J25.3, J26.3, J27.3, J28.3, R33.2, R34.2, R35.2, R36.2, R53.2, R55.1, R57.2, R59.2, R61.2, R63.2, R65.2, R67.2, R69.2, R71.2, U7.2, U10.8, U11.28, U12.24, U12.28, U13.20, U14.20, U15.8, U15.13, U16.2, U16.6, U16.8, U17.8, U18.8, U19.8, U20.8, U21.14, U22.14
+3V3_AON: C2.1, C3.1, R2.2, R3.1, R5.2, U2.1, U2.2, U2.6, U3.2, U4.14
+3V3_RP: C40.1, C41.1, C42.1, C43.1, C44.1, C45.1, C46.1, C47.1, C48.1, C49.1, C50.1, C51.1, C55.1, R73.2, U25.2, U26.8, U27.1, U27.10, U27.22, U27.23, U27.33, U27.42, U27.43, U27.44, U27.48, U27.49, U27.50
+5V_HDR: J2.2, J2.4, Q3.5, U6.4
+5V_PI: C8.1, C9.2, C10.1, C38.2, L1.2, Q3.1, Q3.2, Q3.3, Q15.1, Q15.2, Q15.3, R8.1, U6.3, U6.6, U7.3, U24.3, U24.6
+5V_SERVO: C19.1, J4.2, J5.2, J6.2, J7.2, J8.2, J9.2, J10.2, J11.2, J12.2, J13.2, J14.2, J15.2, J16.2, J17.2, J18.2, J19.2, Q7.5, R15.1, U8.12, U8.24
ACT_DISABLE: R19.1, R28.1, U4.8
ALERT_N: J2.13, R2.1, U2.3, U4.1
ARM: J2.11, R32.1, SW2.1
ARM_SW: R6.1, SW2.2, U4.9
BOOT1_motor: C20.1, U9.26
BOOT1_servo: C12.1, U8.26
BOOT2_motor: C21.1, U9.20
BOOT2_servo: C13.1, U8.20
BOOT_PI: C5.1, U5.1
CC1: J29.A5, R76.1
CC2: J29.B5, R77.1
CMP_FL_A: R57.1, U17.1, U21.1
CMP_FL_B: R59.1, U17.7, U21.3
CMP_FR_A: R61.1, U18.1, U21.5
CMP_FR_B: R63.1, U18.7, U21.9
CMP_REF: R55.2, R56.1, U17.2, U17.6, U18.2, U18.6, U19.2, U19.6, U20.2, U20.6
CMP_RL_A: R69.1, U20.1, U22.1
CMP_RL_B: R71.1, U20.7, U22.3
CMP_RR_A: R65.1, U19.1, U21.11
CMP_RR_B: R67.1, U19.7, U21.13
COMPM_motor: C25.1, R23.2
COMPM_servo: C17.1, R14.2
COMP_PI: R10.1, U5.6
COMP_PI_MID: C6.1, R10.2
COMP_motor: R23.1, U9.9
COMP_servo: R14.1, U8.9
DISB_motor: Q9.2, R28.2
DISB_servo: Q4.2, R19.2
ENC_FL_A: U21.2, U27.4
ENC_FL_B: U21.4, U27.5
ENC_FR_A: U21.6, U27.6
ENC_FR_B: U21.8, U27.7
ENC_INT: J2.16, U27.15
ENC_RL_A: U22.2, U27.11
ENC_RL_B: U22.4, U27.12
ENC_RR_A: U21.10, U27.8
ENC_RR_B: U21.12, U27.9
EN_PI: Q2.3, U5.3
EN_PI_BASE: Q2.2, R11.2
EN_motor: D4.1, Q9.3, R26.2, R27.1, U9.1
EN_servo: D3.1, Q4.3, R17.2, R18.1, U8.1
FAULT: R11.1, U4.3, U4.5
FAULT_N: U4.2, U4.6, U4.10
FB_PI: R8.2, R9.1, U5.5
FB_motor: R24.2, R25.1, U9.11
FB_servo: R15.2, R16.1, U8.11
FL_IN1: U12.10, U13.21
FL_IN2: U12.9, U13.22
FL_N: J20.2, U13.5, U13.6
FL_P: J20.1, U13.1, U13.2
FL_PWM: U12.8, U13.23
FR_IN1: U12.13, U13.17
FR_IN2: U12.12, U13.16
FR_N: J21.2, U13.7, U13.8
FR_P: J21.1, U13.11, U13.12
FR_PWM: U12.11, U13.15
GATE_IN: Q1.4, R1.1, U1.4, U1.5, U2.10
GATE_PI: Q3.4, U6.5
GATE_RP: Q15.4, U24.5
GATE_USB: Q14.4, U23.5
GND: C2.2, C3.2, C4.2, C6.2, C7.2, C8.2, C10.2, C11.2, C14.2, C15.2, C16.2, C17.2, C18.2, C19.2, C22.2, C23.2, C24.2, C25.2, C26.2, C27.2, C28.2, C29.2, C30.2, C31.2, C32.2, C33.2, C34.2, C35.2, C36.2, C39.2, C40.2, C41.2, C42.2, C43.2, C44.2, C45.2, C46.2, C47.2, C48.2, C49.2, C50.2, C51.2, C52.2, C53.2, C54.2, C55.2, D1.2, D2.2, D3.2, D4.2, J1.2, J2.6, J2.9, J2.14, J2.20, J2.25, J2.30, J2.34, J2.39, J3.4, J4.3, J5.3, J6.3, J7.3, J8.3, J9.3, J10.3, J11.3, J12.3, J13.3, J14.3, J15.3, J16.3, J17.3, J18.3, J19.3, J24.2, J25.4, J26.4, J27.4, J28.4, J29.A1, J29.A12, J29.B1, J29.B12, J29.S1, Q2.1, Q4.1, Q9.1, R4.2, R6.2, R7.2, R9.2, R12.2, R13.2, R16.2, R18.2, R20.2, R21.2, R22.2, R25.2, R27.2, R29.2, R32.2, R54.2, R56.2, R58.2, R60.2, R62.2, R64.2, R66.2, R68.2, R70.2, R72.2, R76.2, R77.2, SW1.2, SW3.2, U1.2, U2.7, U4.7, U4.12, U4.13, U5.7, U5.9, U6.2, U7.1, U8.5, U8.10, U8.13, U8.15, U8.22, U8.29, U9.5, U9.10, U9.13, U9.15, U9.22, U9.29, U10.1, U10.2, U10.3, U10.4, U11.1, U11.2, U11.3, U11.4, U11.5, U11.14, U11.24, U11.25, U12.1, U12.2, U12.3, U12.4, U12.5, U12.14, U12.25, U13.3, U13.4, U13.9, U13.10, U13.18, U14.3, U14.4, U14.9, U14.10, U14.18, U15.1, U15.9, U15.11, U15.18, U16.1, U16.5, U16.7, U17.4, U18.4, U19.4, U20.4, U21.7, U22.5, U22.7, U22.9, U22.11, U22.13, U23.2, U24.2, U25.1, U26.4, U27.19, U27.57, Y1.2, Y1.4
HDRV1_motor: Q10.4, U9.27
HDRV1_servo: Q5.4, U8.27
HDRV2_motor: Q12.4, U9.19
HDRV2_servo: Q7.4, U8.19
I2C1_SCL: J24.4, R31.2, U2.5, U11.26, U12.26, U15.23, U16.4, U27.14
I2C1_SDA: J24.3, R30.2, U2.4, U11.27, U12.27, U15.24, U16.3, U27.13
I2C_SCL_PI: J2.5, R31.1
I2C_SDA_PI: J2.3, R30.1
ID_SC: J2.28, R34.1, U10.6
ID_SD: J2.27, R33.1, U10.5
IMU_INT: J2.15, U15.12
ISNS_motor: Q11.1, Q11.2, Q11.3, Q13.1, Q13.2, Q13.3, R29.1, U9.14, U9.16
ISNS_servo: Q6.1, Q6.2, Q6.3, Q8.1, Q8.2, Q8.3, R20.1, U8.14, U8.16
LDRV1_motor: Q11.4, U9.25
LDRV1_servo: Q6.4, U8.25
LDRV2_motor: Q13.4, U9.21
LDRV2_servo: Q8.4, U8.21
LED0: R37.1, U11.6
LED1: R38.1, U11.7
LED2: R39.1, U11.8
LED3: R40.1, U11.9
LED4: R41.1, U11.10
LED5: R42.1, U11.11
LED6: R43.1, U11.12
LED7: R44.1, U11.13
LED8: R45.1, U11.15
LED9: R46.1, U11.16
LED10: R47.1, U11.17
LED11: R48.1, U11.18
LED12: R49.1, U11.19
LED13: R50.1, U11.20
LED14: R51.1, U11.21
LED15: R52.1, U11.22
LR8_ADJ: R3.2, R4.1, U3.3
MODE_motor: R22.1, U9.4
MODE_servo: R13.1, U8.4
MOTOR_OE: R53.1, U12.23, U27.16
MOTOR_STBY: R54.1, U13.19, U14.19, U27.3
MPU_CP: C34.1, U15.20
MPU_REG: C33.1, U15.10
PPS: J2.12, J3.3
QSPI_SCK: U26.6, U27.52
QSPI_SD0: U26.5, U27.53
QSPI_SD1: U26.2, U27.55
QSPI_SD2: U26.3, U27.54
QSPI_SD3: U26.7, U27.51
QSPI_SS: SW3.1, U26.1, U27.56
RESET_N: C4.1, R5.1, SW1.1, U4.4
RL_IN1: U12.20, U14.17
RL_IN2: U12.19, U14.16
RL_N: J23.2, U14.7, U14.8
RL_P: J23.1, U14.11, U14.12
RL_PWM: U12.18, U14.15
RP_5V: C39.1, Q14.5, Q15.5, U23.4, U24.4, U25.3
RR_IN1: U12.17, U14.21
RR_IN2: U12.16, U14.22
RR_N: J22.2, U14.5, U14.6
RR_P: J22.1, U14.1, U14.2
RR_PWM: U12.15, U14.23
RT_PI: R7.1, U5.4
RT_motor: R21.1, U9.6
RT_servo: R12.1, U8.6
RUN: R73.1, U27.26
SERVO_OE: R36.1, U11.23, U27.2
SERVO_SIG_0: J4.1, R37.2
SERVO_SIG_1: J5.1, R38.2
SERVO_SIG_2: J6.1, R39.2
SERVO_SIG_3: J7.1, R40.2
SERVO_SIG_4: J8.1, R41.2
SERVO_SIG_5: J9.1, R42.2
SERVO_SIG_6: J10.1, R43.2
SERVO_SIG_7: J11.1, R44.2
SERVO_SIG_8: J12.1, R45.2
SERVO_SIG_9: J13.1, R46.2
SERVO_SIG_10: J14.1, R47.2
SERVO_SIG_11: J15.1, R48.2
SERVO_SIG_12: J16.1, R49.2
SERVO_SIG_13: J17.1, R50.2
SERVO_SIG_14: J18.1, R51.2
SERVO_SIG_15: J19.1, R52.2
SLOPE_motor: C24.1, U9.7
SLOPE_servo: C16.1, U8.7
SNS_FL_A: J25.1, R58.1, U17.3
SNS_FL_B: J25.2, R60.1, U17.5
SNS_FR_A: J26.1, R62.1, U18.3
SNS_FR_B: J26.2, R64.1, U18.5
SNS_RL_A: J28.1, R70.1, U20.3
SNS_RL_B: J28.2, R72.1, U20.5
SNS_RR_A: J27.1, R66.1, U19.3
SNS_RR_B: J27.2, R68.1, U19.5
SS_motor: C23.1, U9.8
SS_servo: C15.1, U8.8
SW1_motor: C20.2, L3.1, Q10.1, Q10.2, Q10.3, Q11.5, U9.28
SW1_servo: C12.2, L2.1, Q5.1, Q5.2, Q5.3, Q6.5, U8.28
SW2_motor: C21.2, L3.2, Q12.1, Q12.2, Q12.3, Q13.5, U9.18
SW2_servo: C13.2, L2.2, Q7.1, Q7.2, Q7.3, Q8.5, U8.18
SW_PI: C5.2, D2.1, L1.1, U5.8
UART_RX: J2.10, J3.2
UART_TX: J2.8, J3.1
USB_DM: J29.A7, J29.B7, R74.2
USB_DM_C: R74.1, U27.46
USB_DP: J29.A6, J29.B6, R75.2
USB_DP_C: R75.1, U27.47
VBAT_FUSED: C1.2, D1.1, F1.2, Q1.1, Q1.2, Q1.3, U1.3, U1.6
VBAT_LOAD: C7.1, C18.1, C26.1, Q5.5, Q10.5, R1.2, R17.1, R26.1, U2.8, U2.9, U3.1, U5.2, U8.2, U8.3, U9.2, U9.3
VBAT_RAW: F1.1, J1.1
VBUS: C37.2, J29.A4, J29.A9, J29.B4, J29.B9, Q14.1, Q14.2, Q14.3, U23.3, U23.6
VCAP_IN: C1.1, U1.1
VCAP_PI: C9.1, U6.1
VCAP_RP: C38.1, U24.1
VCAP_USB: C37.1, U23.1
VCC_motor: C22.1, U9.23
VCC_servo: C14.1, U8.23
VM_MOTOR: C27.1, C31.1, C32.1, Q12.5, R24.1, U9.12, U9.24, U13.13, U13.14, U13.24, U14.13, U14.14, U14.24
VREG_1V1: C52.1, U27.45
WP: R35.1, U10.7
XIN: C53.1, U27.20, Y1.1
XOUT: C54.1, U27.21, Y1.3

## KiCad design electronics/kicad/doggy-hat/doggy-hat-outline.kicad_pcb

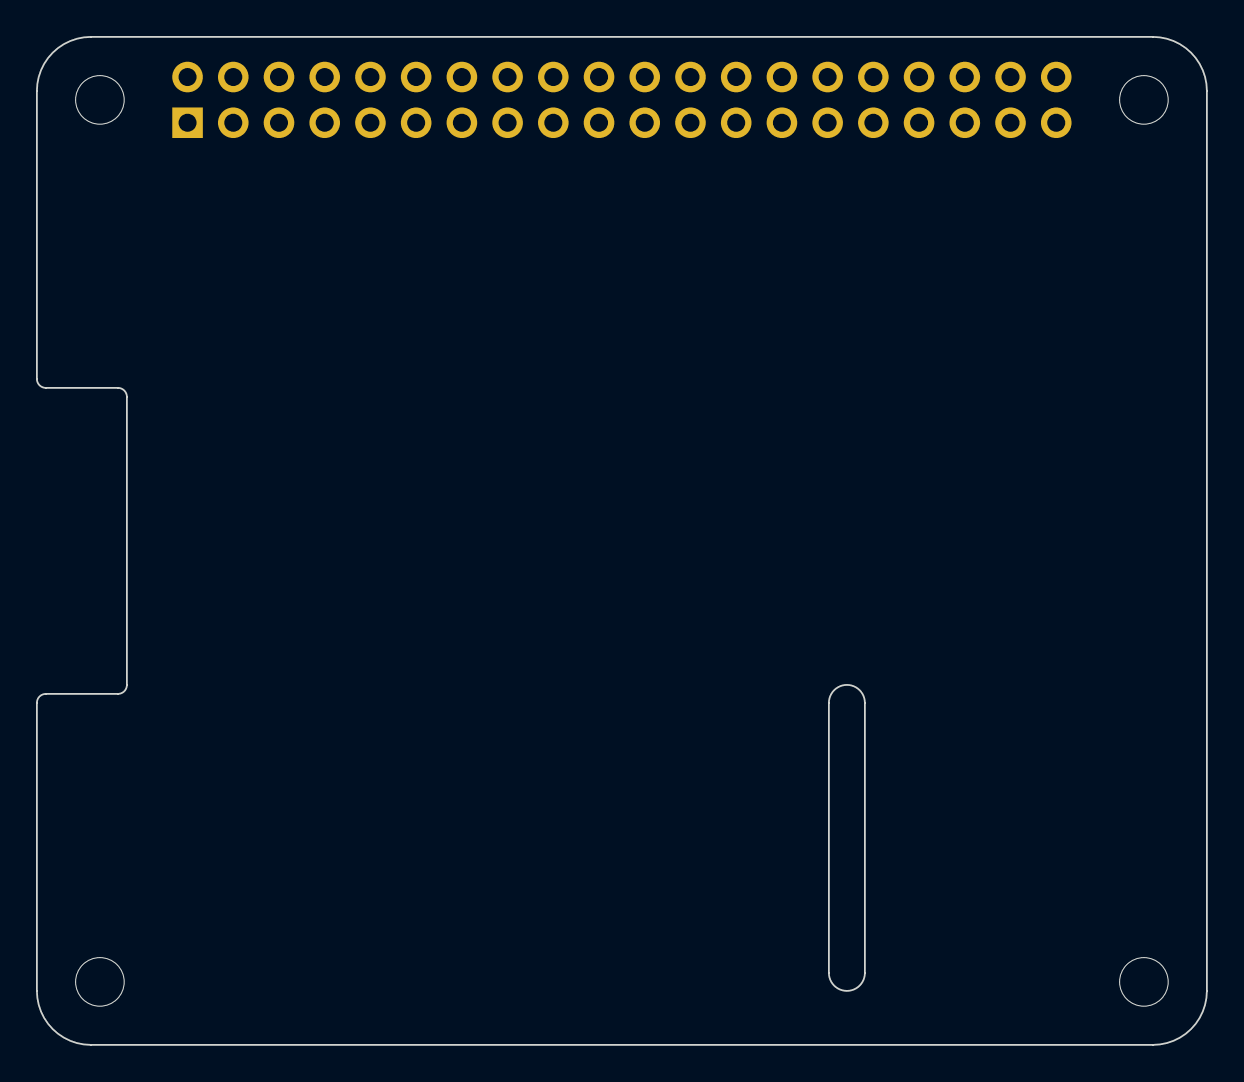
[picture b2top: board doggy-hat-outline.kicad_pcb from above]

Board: 2 copper layers, 65.0 x 56.0 mm, 5 parts (1 on the bottom side), 3 nets, no tracks yet.

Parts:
J1: GPIO; PinSocket_2x20_P2.54mm_Vertical
MH1, MH2, MH3, MH4: MountingHole_2.7mm_M2.5

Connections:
+3V3: J1.1, J1.17
+5V: J1.2, J1.4
GND: J1.6, J1.9, J1.14, J1.20, J1.25, J1.30, J1.34, J1.39

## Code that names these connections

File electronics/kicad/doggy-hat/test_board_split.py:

"""The hat is two boards. Pack current crosses J30, not the GPIO header."""

import os
import re
import subprocess

# ================================================================================
DIR = os.path.dirname(os.path.abspath(__file__))
KICAD = os.path.dirname(DIR)

# ================================================================================
def export(name):
    root = os.path.join(KICAD, name, name + ".kicad_sch")
    dest = os.path.join("/tmp", name + "-split.net")
    subprocess.check_call([
        "kicad-cli", "sch", "export", "netlist",
        "--format", "kicadsexpr",
        "-o", dest, root,
    ])
    with open(dest, encoding="utf-8") as handle:
        return handle.read()

# ================================================================================
def components(text):
    return set(re.findall(r'\(comp \(ref "([^"]+)"\)', text))

# ================================================================================
def nets(text):
    found = {}
    for chunk in text.split("(net (code ")[1:]:
        name = re.search(r'\(name "([^"]*)"', chunk).group(1)
        nodes = re.findall(r'\(node \(ref "([^"]+)"\) \(pin "([^"]+)"\)', chunk)
        found[name] = nodes
    return found

# ================================================================================
def pins_of(netmap, ref):
    found = {}
    for name, nodes in netmap.items():
        for node_ref, pin in nodes:
            if node_ref == ref:
                found[int(pin)] = name
    return found

# ================================================================================
def require(condition, message):
    if condition == False:
        raise AssertionError(message)

# ================================================================================
def check_j30(netmap, pin19):
    pins = pins_of(netmap, "J30")
    for pin in range(1, 9):
        require(pins.get(pin) == "VBAT_LOAD", "J30 pin " + str(pin))
    for pin in (9, 10, 11, 12, 13, 14, 15, 16, 20):
        require(pins.get(pin) == "GND", "J30 ground " + str(pin))
    require(pins.get(17) == "+3V3" and pins.get(18) == "+3V3", "J30 3V3")
    require(pins.get(19) == pin19, "J30 pin 19")
    require(pins.get(21) == "I2C1_SDA" and pins.get(22) == "I2C1_SCL", "J30 I2C")
    require(pins.get(23) == "+5V_PI" and pins.get(24) == "+5V_PI", "J30 5V")

# ================================================================================
def check_lower(text):
    refs = components(text)
    for ref in ("J1", "J2", "J30", "U2", "U10", "U15", "U16"):
        require(ref in refs, "lower missing " + ref)
    for ref in ("U11", "U27", "J6", "SW2"):
        require(ref not in refs, "lower should not have " + ref)
    netmap = nets(text)
    check_j30(netmap, "ACT_DISABLE")
    arm = set(ref for ref, _pin in netmap["ARM"])
    require("U4" in arm and "J2" in arm and "SW2" not in arm, "ARM")
    require("U10" in set(ref for ref, _pin in netmap["ID_SD"]), "ID_SD")
    header = pins_of(netmap, "J2")
    require(header[3] == "I2C_SDA_PI" and header[16] == "ENC_INT", "lower header")
    require("U15" in set(ref for ref, _pin in netmap["I2C1_SDA"]), "IMU on device I2C")

# ================================================================================
def check_upper(text):
    refs = components(text)
    for ref in ("J2", "J6", "J20", "J30", "SW2", "U11", "U27", "R78"):
        require(ref in refs, "upper missing " + ref)
    for ref in ("J1", "U2", "U10", "U15"):
        require(ref not in refs, "upper should not have " + ref)
    netmap = nets(text)
    check_j30(netmap, "ACT_LATCH")
    disable = set(ref for ref, _pin in netmap["ACT_DISABLE"])
    require("SW2" in disable and "R78" in disable and "R19" in disable, "e-stop")
    require("J24" not in disable, "e-stop shorted to 3V3")
    require("ID_SD" not in netmap, "ID bus on the upper board")
    header = pins_of(netmap, "J2")
    require(header[2] == "+5V_HDR" and header[4] == "+5V_HDR", "header 5V")
    require(header[16] == "ENC_INT", "ENC_INT")
    for pin in (3, 5, 27, 28):
        require(header[pin].startswith("unconnected-"), "upper header pin " + str(pin))
    pi = set(ref for ref, _pin in netmap["+5V_PI"])
    hdr = set(ref for ref, _pin in netmap["+5V_HDR"])
    require(len(pi.intersection(hdr)) == 0, "+5V_PI joined to +5V_HDR")

# ================================================================================
def check_pack_estop():
    path = os.path.join(DIR, "pack.kicad_sch")
    with open(path, encoding="utf-8") as handle:
        text = handle.read()
    require("ARM_SW" not in text, "ARM_SW still on the pack sheet")
    require('(property "Reference" "SW2"' not in text, "SW2 still on the pack sheet")
    require("U4" in text and "J1" in text, "pack sheet lost its parts")

# ================================================================================
def main():
    check_pack_estop()
    check_lower(export("doggy-lower"))
    check_upper(export("doggy-upper"))
    print("board split ok")

# ================================================================================
if __name__ == "__main__":
    main()

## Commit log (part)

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2025-07-10 Starting
2025-07-11 Initial stuff for dealing with PWM chip
2025-07-12 Working angles with SG92R servo
2025-07-17 Initial classess for Freenove Dog
2025-07-18 Starting work with IMU
2025-07-18 Accelerometer showing reasonable values
2025-07-19 Gyro and temperature
2025-07-20 Start homing waist
